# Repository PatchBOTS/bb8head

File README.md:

# BB-8 Head Mechanism
### Please Read Before Downloading 3D File

I'm happy to distribute these files for free but they are not gauranteed to work.  I very big on the "print quick and dirty and fix later" philosophy, so there may be some physcial editing to the parts needed which I did not document.

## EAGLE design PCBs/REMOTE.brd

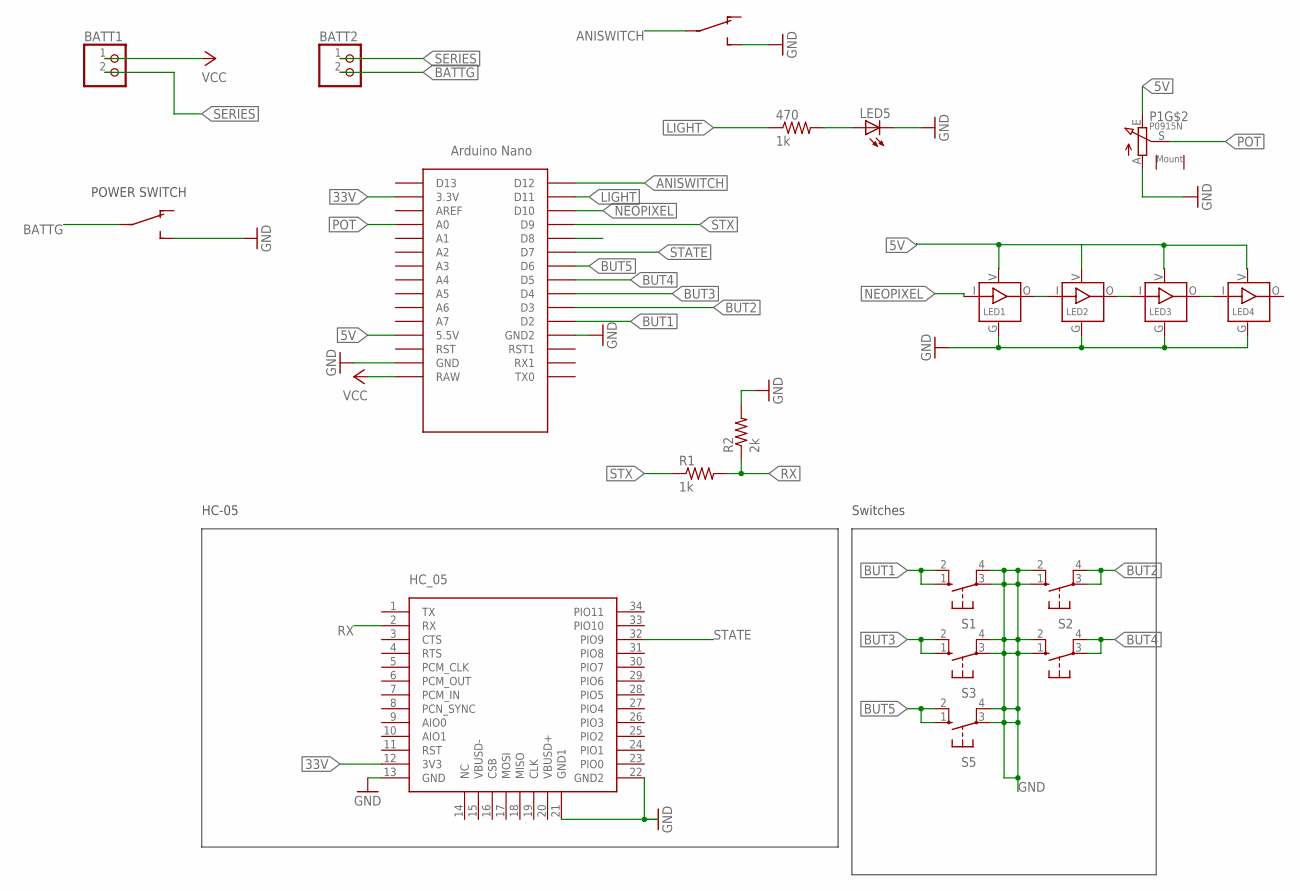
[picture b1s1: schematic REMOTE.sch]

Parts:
470: 1k; R2010
BATT1, BATT2: PINHD-1X2; 1X02
LED1, LED2, LED3, LED4: SK6812_3535; LED3535
LED5: LED3MM
P1: P0915N
POWER, POWER1: DPDT_JS202011CQN
R1: 1k; R2010
R2: 2k; R2010
S1, S2, S3, S4, S5: 10-XX; B3F-10XX
U2: HC_05; BLUETOOTH_SMD
U$1: NANO

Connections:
5V: LED1.V (VDD), LED2.V (VDD), LED3.V (VDD), LED4.V (VDD), P1.E, U$1.5V (5.5V)
33V: U2.12 (3V3), U$1.3.3V
ANISWITCH: POWER1.2, U$1.D12
BATTG: BATT2.2, POWER.2
BUT1: S1.1 (S), S1.2 (S1), U$1.D2
BUT2: S2.3, S2.4 (P1), U$1.D3
BUT3: S3.1 (S), S3.2 (S1), U$1.D4
BUT4: S4.3, S4.4 (P1), U$1.D5
BUT5: S5.1 (S), S5.2 (S1), U$1.D6
GND: LED1.G (GND), LED2.G (GND), LED3.G (GND), LED4.G (GND), LED5.K (C), P1.A, POWER.3 (O2), POWER1.3 (O2), R2.2, S1.3, S1.4 (P1), S2.1 (S), S2.2 (S1), S3.3, S3.4 (P1), S4.1 (S), S4.2 (S1), S5.3, S5.4 (P1), U2.13 (GND), U2.21 (GND1), U2.22 (GND2), U$1.GND, U$1.GND1 (GND2)
LIGHT: 470.1, U$1.D11
unnamed: LED1.O (DO), LED2.I (DI)
unnamed: LED2.O (DO), LED3.I (DI)
unnamed: LED3.O (DO), LED4.I (DI)
unnamed: 470.2, LED5.A
NEOPIXEL: LED1.I (DI), U$1.D10
POT: P1.S, U$1.A0
RX: R1.2, R2.1, U2.2 (RX)
SERIES: BATT1.2, BATT2.1
STATE: U2.32 (PIO9), U$1.D7
STX: R1.1, U$1.D9
VCC: BATT1.1, U$1.RAW

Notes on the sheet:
Switches
HC-05
POWER SWITCH

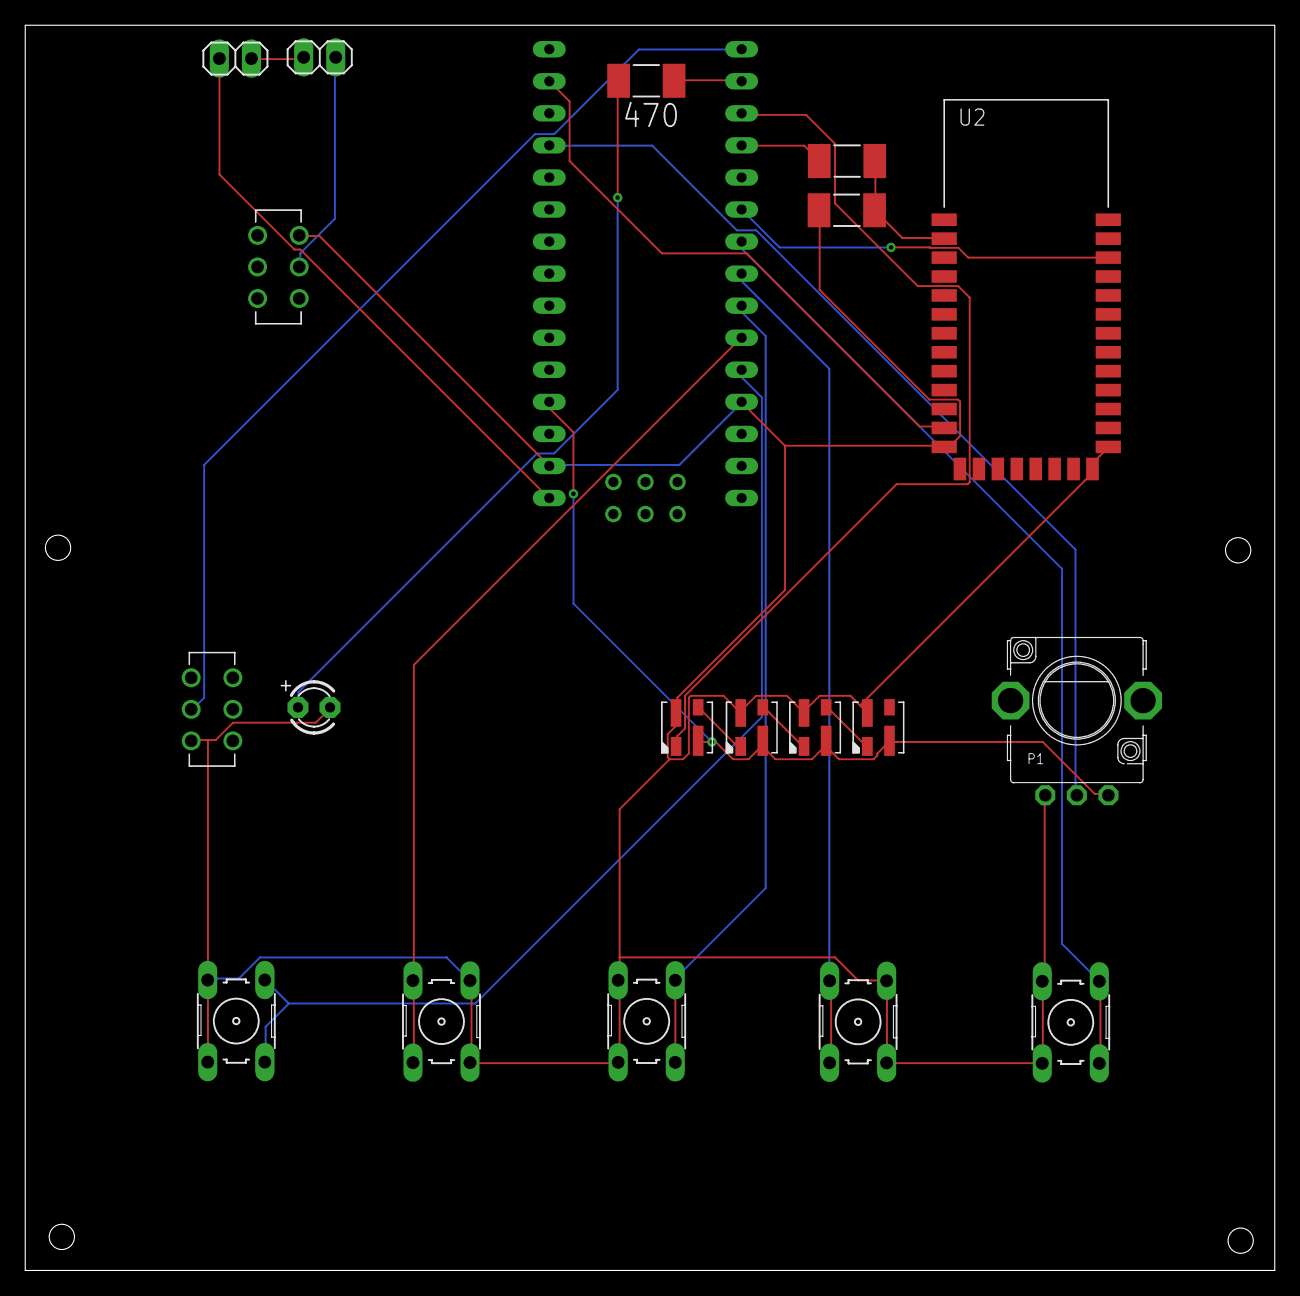
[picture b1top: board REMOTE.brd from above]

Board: 2 copper layers, 99.0 x 98.7 mm, 20 parts (0 on the bottom side), 22 nets.

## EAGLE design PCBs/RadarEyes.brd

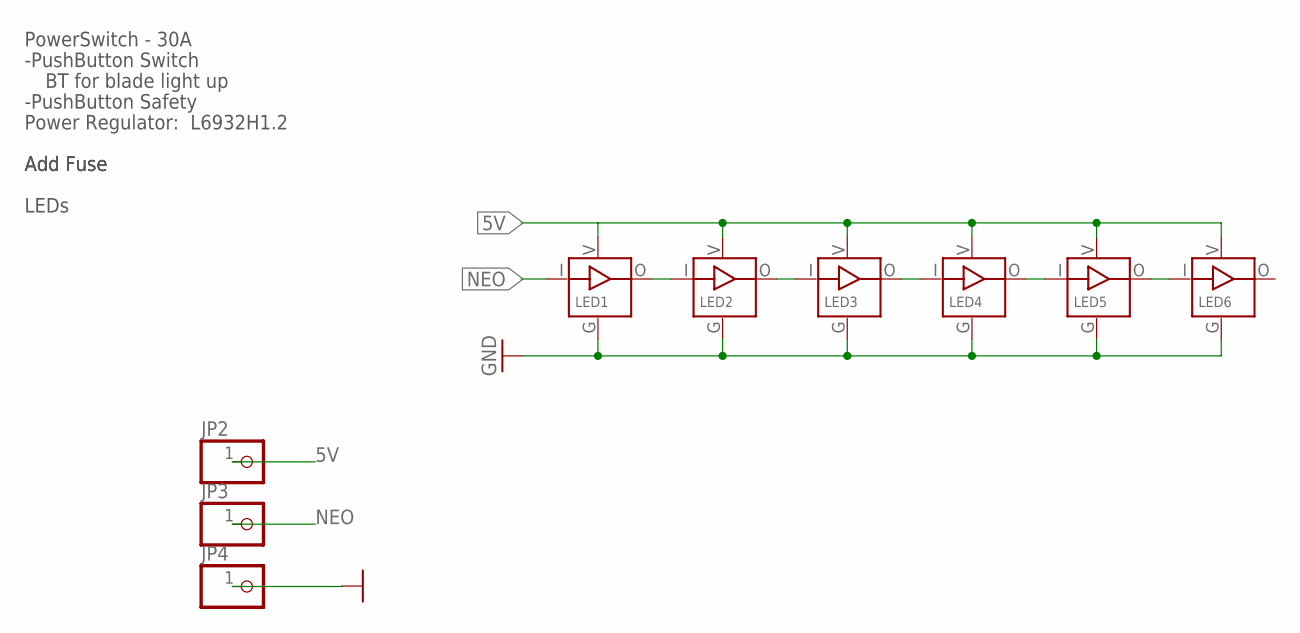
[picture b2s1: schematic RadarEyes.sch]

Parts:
JP2, JP3, JP4: PINHD-1X1; 1X01
LED1, LED2, LED3, LED4, LED5, LED6: SK6812_3535; LED3535

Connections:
5V: JP2.1, LED1.V (VDD), LED2.V (VDD), LED3.V (VDD), LED4.V (VDD), LED5.V (VDD), LED6.V (VDD)
GND: JP4.1, LED1.G (GND), LED2.G (GND), LED3.G (GND), LED4.G (GND), LED5.G (GND), LED6.G (GND)
unnamed: LED1.O (DO), LED2.I (DI)
unnamed: LED2.O (DO), LED3.I (DI)
unnamed: LED3.O (DO), LED4.I (DI)
unnamed: LED4.O (DO), LED5.I (DI)
unnamed: LED5.O (DO), LED6.I (DI)
NEO: JP3.1, LED1.I (DI)

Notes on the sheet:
Power Regulator: L6932H1.2
Add Fuse
-PushButton Switch
-PushButton Safety
LEDs
PowerSwitch - 30A
BT for blade light up

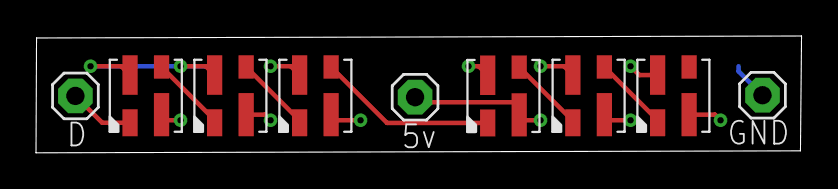
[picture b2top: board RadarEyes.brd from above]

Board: 2 copper layers, 42.5 x 6.5 mm, 9 parts (0 on the bottom side), 8 nets.

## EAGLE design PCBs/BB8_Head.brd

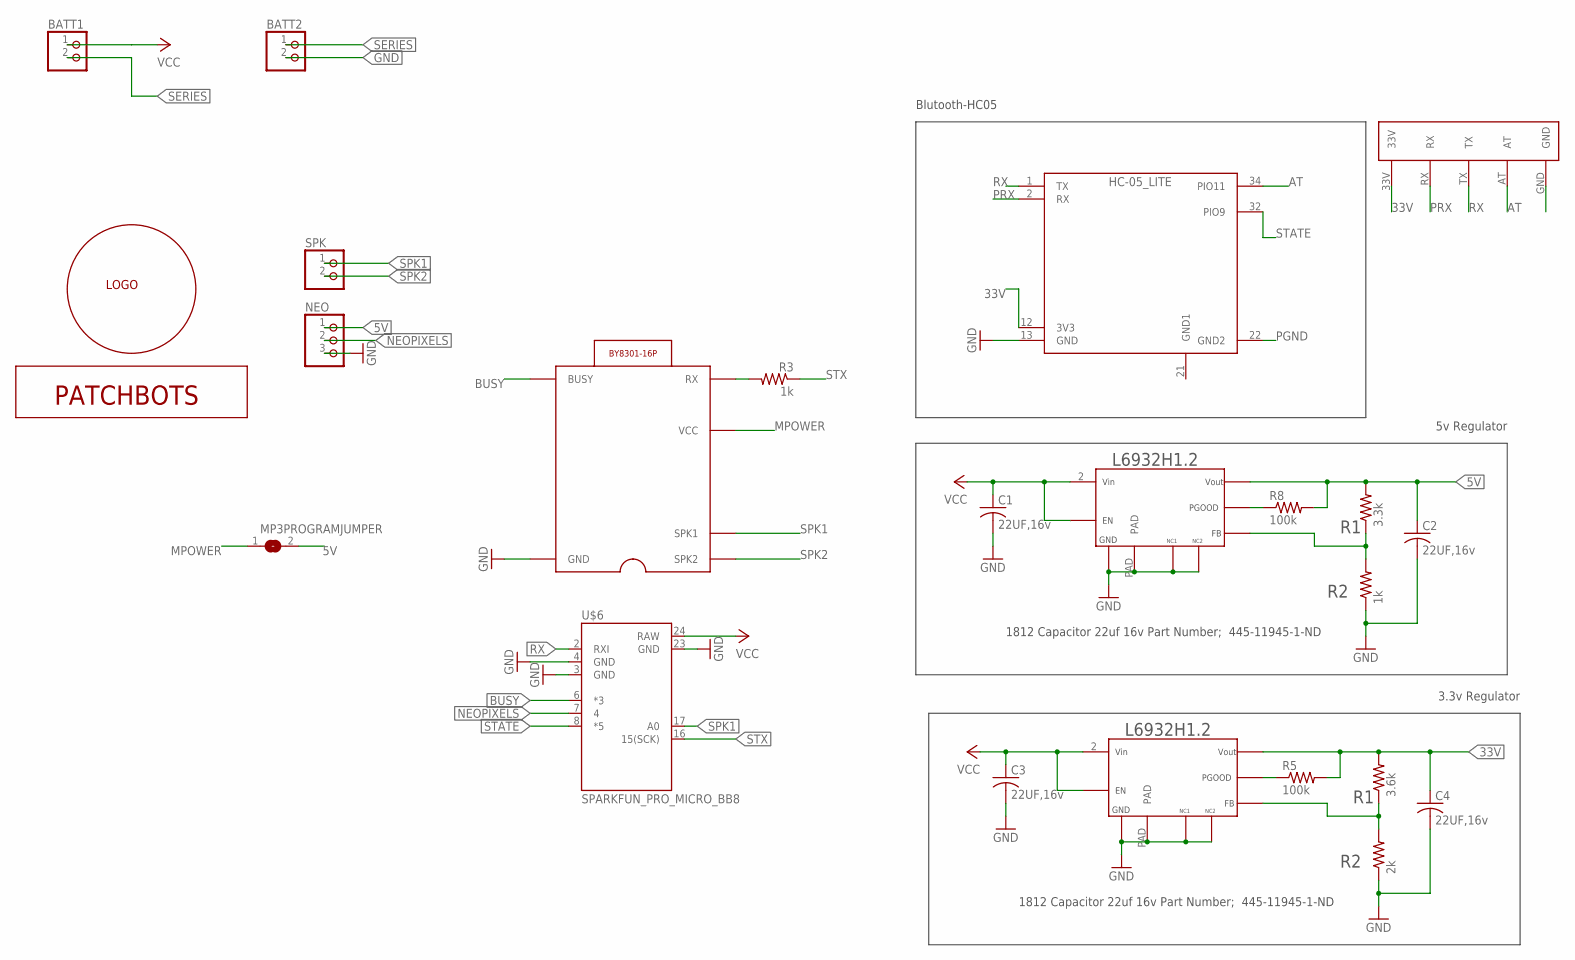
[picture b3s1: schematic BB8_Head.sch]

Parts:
BATT1, BATT2: PINHD-1X2; 1X02
C1, C2, C3, C4: 22UF,16v; C1812
HC-05: HC-05_LITE; BLUETOOTH_SMD_LITE
MP3PROGRAMJUMPER: SJ
NEO: PINHD-1X3; 1X03
R1: 3.3k; R2010
R3, R9: 1k; R2010
R5, R8: 100k; R2010
R6: 3.6k; R2010
R7: 2k; R2010
SPK: PINHD-1X2; 1X02
U$2: LOGO_15MM-MIXED; LOGO_15MM_MIXED
U$3, U$5: L6932H1.2; L6932H1
U$4: PATCHBOTS_SPLIT15MM
U$6: SPARKFUN_PRO_MICRO_BB8
U$7: PROGRAMMER; BLUETOOTH_SMD_PROGRAMMER
U$8: BY8301_BB8; BY8301-16P_BB8

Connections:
5V: C2.1, MP3PROGRAMJUMPER.2, NEO.1, R1.2, R8.2, U$3.4
33V: C4.1, HC-05.12 (3V3), R5.2, R6.2, U$5.4, U$7.33V
AT: HC-05.34 (PIO11), U$7.AT
BUSY: U$6.6 (*3), U$8.BUSY
GND: BATT2.2, C1.2, C2.2, C3.2, C4.2, HC-05.13 (GND), NEO.3, R7.1, R9.1, U$3.6, U$3.7, U$3.8, U$3.PAD, U$5.6, U$5.7, U$5.8, U$5.PAD, U$6.3 (GND), U$6.4 (GND), U$6.23 (GND), U$8.GND
MPOWER: MP3PROGRAMJUMPER.1, U$8.VCC
unnamed: R1.1, R9.2, U$3.3
unnamed: R8.1, U$3.5
unnamed: R5.1, U$5.5
unnamed: R6.1, R7.2, U$5.3
unnamed: R3.2, U$8.RX
NEOPIXELS: NEO.2, U$6.7 (4)
PGND: HC-05.22 (GND2), U$7.GND
PRX: HC-05.2 (RX), U$7.RX
RX: HC-05.1 (TX), U$6.2 (RXI), U$7.TX
SERIES: BATT1.2, BATT2.1
SPK1: SPK.1, U$6.17 (A0), U$8.SPK1
SPK2: SPK.2, U$8.SPK2
STATE: HC-05.32 (PIO9), U$6.8 (*5)
STX: R3.1, U$6.16 (15(SCK))
VCC: BATT1.1, C1.1, C3.1, U$3.1, U$3.2, U$5.1, U$5.2, U$6.24 (RAW)

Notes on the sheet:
1812 Capacitor 22uf 16v Part Number; 445-11945-1-ND
5v Regulator
3.3v Regulator
Blutooth-HC05

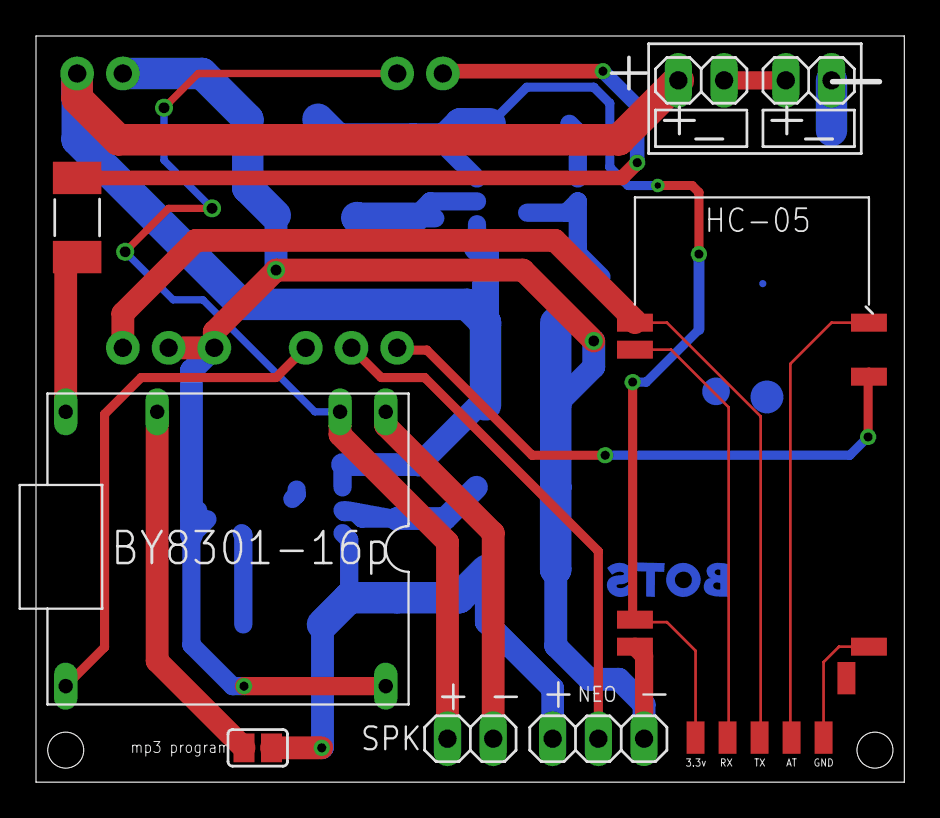
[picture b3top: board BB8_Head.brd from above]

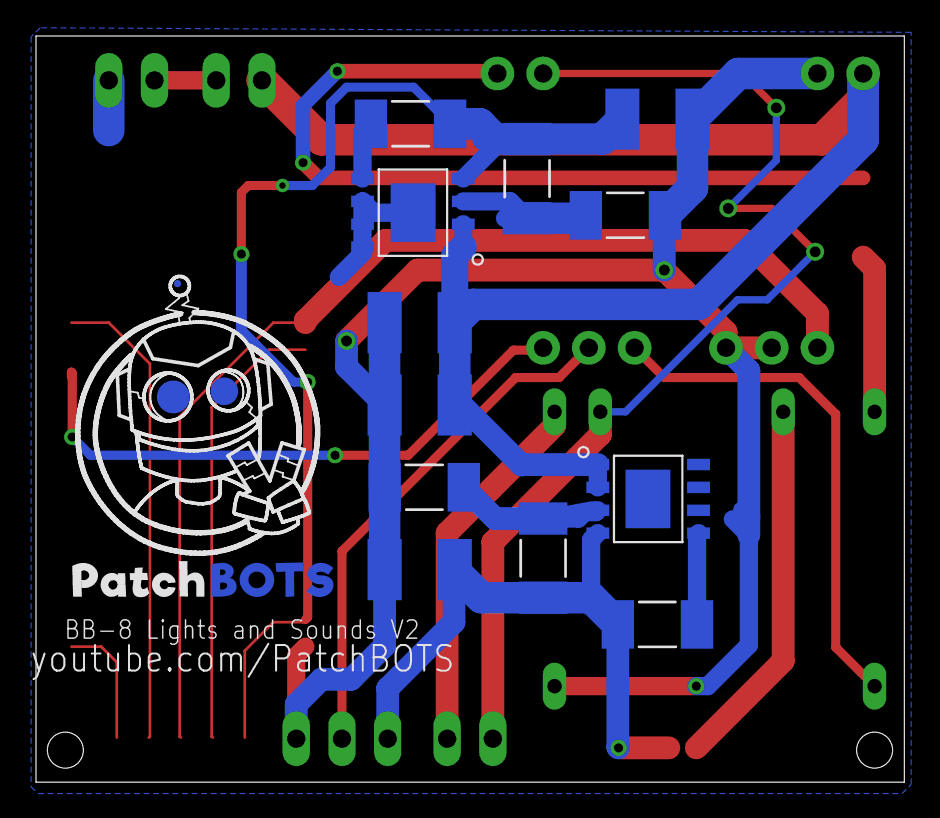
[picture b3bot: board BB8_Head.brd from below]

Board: 2 copper layers, 48.2 x 41.5 mm, 24 parts (14 on the bottom side), 21 nets.

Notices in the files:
parts and their libraries:
SparkFun-Boards: Licensing: Creative Commons ShareAlike 4.0 International - https://creativecommons.org/licenses/by-sa/4.0
